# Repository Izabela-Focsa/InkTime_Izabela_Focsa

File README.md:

# InkTime Smartwatch - Dispozitiv Wearable Open Source (Stadiu EVT)

## 📌 Prezentare Generală

**InkTime** este un smartwatch open-source, proiectat în jurul microcontrolerului **Nordic nRF52840**, cu accent pe consum redus de energie, conectivitate Bluetooth Low Energy și modularitate hardware.

Acest repository conține:

* designul PCB (Fusion Electronics)
* fișierele pentru fabricație (Gerber, BOM, Pick & Place)
* designul mecanic (Fusion 360)
* integrarea sistemului pentru etapa EVT (Engineering Validation Test)

---

## 🧩 Diagrama Bloc a Sistemului

Arhitectura sistemului este centrată în jurul microcontrolerului nRF52840, care gestionează comunicația, afișajul și senzorii.

```
        +----------------------+
        |     Baterie LiPo     |
        +----------+-----------+
                   |
            +------v------+
            |  BQ25180    |  (Încărcare)
            +------+------+
                   |
            +------v------+
            |  RT6160A    |  (Regulator 3.3V)
            +------+------+
                   |
         +---------v---------+
         |    nRF52840 MCU   |
         | (BLE + Procesare) |
         +---+----+----+-----+
             |    |    |
        SPI  |    |    | I2C
             |    |    |
   +---------v+  |   +v-----------+
   | Display   |  |   | BMA423 IMU|
   | E-Paper   |  |   +------------+
   +----------+  |
                 |
             +---v---------+
             | MAX17048    |
             | Fuel Gauge  |
             +-------------+

             +-------------+
             | DRV2605L    |
             | Vibrații    |
             +-------------+

             +-------------+
             | Butoane     |
             +-------------+
```

---

## 🔌 Funcționalitatea Hardware (Detaliat)

### 🧠 Microcontroler – nRF52840

* ARM Cortex-M4F @ 64 MHz
* Bluetooth Low Energy 5.0 integrat
* Consum foarte redus în mod sleep

Roluri principale:

* procesare date senzori
* control display
* comunicare BLE

---

### 📺 Display – E-Paper

* Interfață: **SPI**
* Consum foarte mic
* Ideal pentru afișare permanentă

---

### ⚡ Managementul Energiei

#### 🔋 BQ25180

* gestionează încărcarea bateriei LiPo
* alimentare prin USB (VBUS)

#### 🔌 RT6160A

* convertor Buck-Boost
* furnizează **3.3V stabil**
* permite funcționarea chiar și la tensiuni scăzute ale bateriei

---

### 📊 Senzori și Actuatori

#### BMA423 (Accelerometru)

* interfață I2C
* detectare mișcare / pași

#### MAX17048 (Fuel Gauge)

* monitorizare nivel baterie
* consum foarte redus

#### DRV2605L (Driver Haptic)

* controlează motorul de vibrații
* suportă feedback haptic avansat

---

### 🎮 Input Utilizator

* 3 butoane: UP / ENTER / DOWN
* conectate ca GPIO cu rezistențe pull-up interne

---

## 🔗 Mapare Pini nRF52840

| Componentă          | Pini                                                                          | Interfață | Motiv                  |
| ------------------- | ----------------------------------------------------------------------------- | --------- | ---------------------- |
| **Display E-Paper** | P0.28 (SCK), P0.29 (MOSI), P0.30 (CS), P0.31 (D/C), P0.02 (RST), P0.03 (BUSY) | SPI       | Transfer rapid de date |
| **Butoane**         | P0.08, P0.11, P0.12                                                           | GPIO      | Input simplu           |
| **Haptic Driver**   | P0.16                                                                         | GPIO/PWM  | Control vibrații       |
| **Senzori I2C**     | P0.14 (SDA), P0.15 (SCL)                                                      | I2C       | Magistrală comună      |
| **Fuel Gauge**      | I2C                                                                           | I2C       | Monitorizare baterie   |

---

## 📦 Bill of Materials (BOM)

| Ref  | Componentă | Link JLCPCB                                             | Datasheet                                                                                      |
| ---- | ---------- | ------------------------------------------------------- | ---------------------------------------------------------------------------------------------- |
| U1   | nRF52840   | https://jlcpcb.com/partdetail/Nordic-nRF52840           | https://infocenter.nordicsemi.com/pdf/nRF52840_PS_v1.1.pdf                                     |
| U2   | DRV2605L   | https://jlcpcb.com/partdetail/TexasInstruments-DRV2605L | https://www.ti.com/lit/ds/symlink/drv2605l.pdf                                                 |
| U3   | MAX17048   | https://jlcpcb.com/partdetail/MaximIntegrated-MAX17048  | https://datasheets.maximintegrated.com/en/ds/MAX17048-MAX17049.pdf                             |
| IC1  | BQ25180    | https://jlcpcb.com/partdetail/TexasInstruments-BQ25180  | https://www.ti.com/lit/ds/symlink/bq25180.pdf                                                  |
| IC2  | BMA423     | https://jlcpcb.com/partdetail/Bosch-BMA423              | https://www.bosch-sensortec.com/media/boschsensortec/downloads/datasheets/bst-bma423-ds000.pdf |
| IC3  | RT6160A    | https://jlcpcb.com/partdetail/Richtek-RT6160A           | https://www.richtek.com/assets/product_file/RT6160A/DS6160A-00.pdf                             |
| ANT1 | Antenă BLE | https://jlcpcb.com                                      |                                                                          |

---

## ⚙️ Constrângeri și Decizii de Design

### PCB

* trasee alimentare: **0.3 mm**
* trasee semnal: **0.15 mm**
* PCB pe 2 straturi

### RF

* plan de masă continuu
* zonă fără cupru sub antenă

### Decuplare

* condensatori 100nF la <1mm de fiecare IC

### Mecanic

* toate componentele pe **TOP layer**
* design compact pentru carcasă

---

## 🔋 Estimare Consum Energetic

| Mod                   | Consum    |
| --------------------- | --------- |
| Activ (BLE + display) | ~15–20 mA |
| Idle                  | ~2–5 mA   |
| Sleep                 | <10 µA    |

Baterie: ~200–300 mAh
Autonomie estimată: **2–5 zile**

---

## 🖼️ Randări și Design

Randările dispozitivului, ale PCB-ului și integrarea în carcasă pot fi găsite în folderul dedicat din repository:

👉 [Images Folder](./Images)

---

## 🛠️ Fișiere pentru Fabricație

* Gerber
* Drill files
* Pick & Place (.csv)
* BOM (.csv)

---

## 📘 Design Log

* realizare schemă electronică
* rutare PCB completă
* verificare DRC
* integrare mecanică finală

---

## 📄 Licență

Proiectul este licențiat sub **GNU General Public License v3.0**.

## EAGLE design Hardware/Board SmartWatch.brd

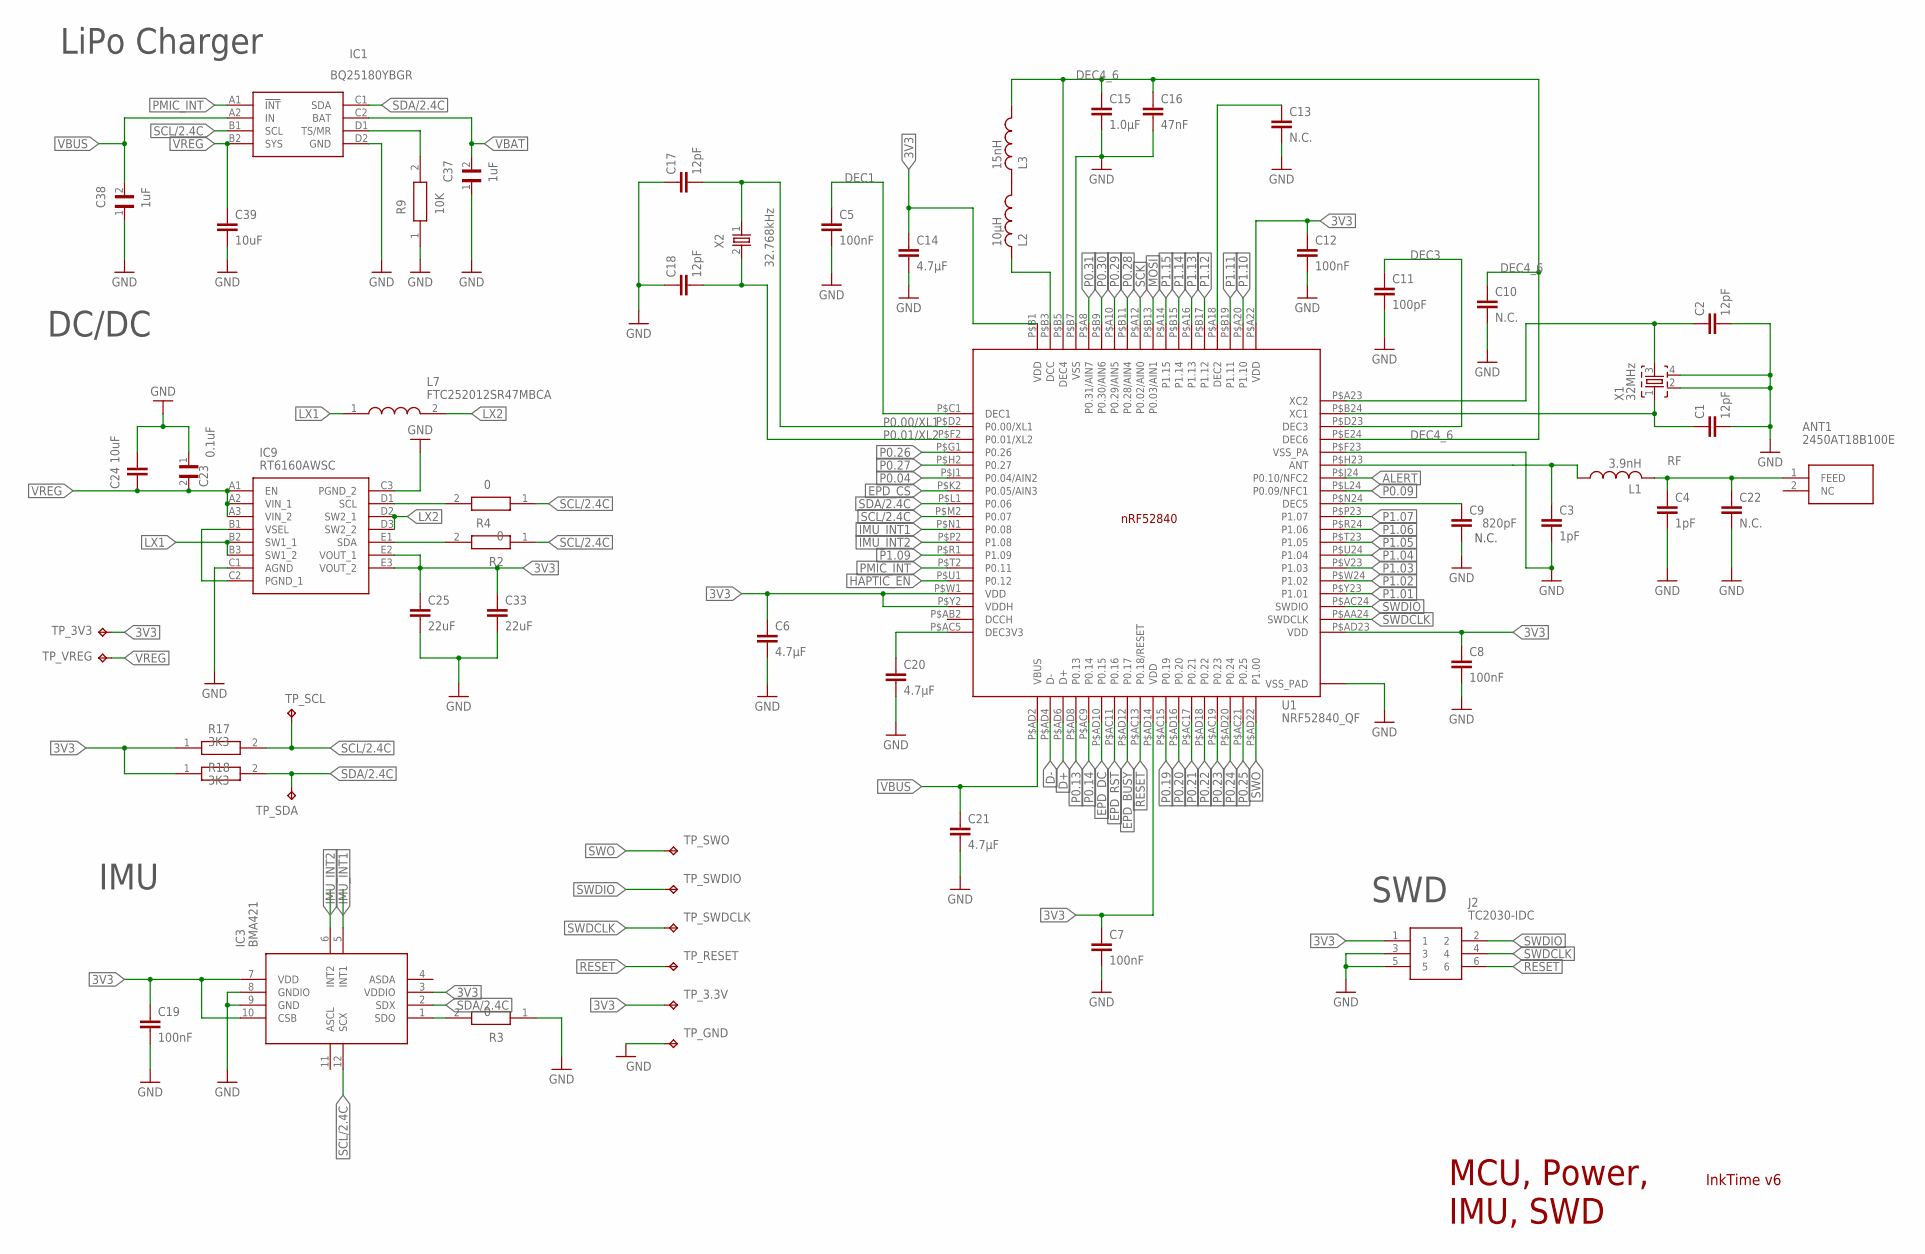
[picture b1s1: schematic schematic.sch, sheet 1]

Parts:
ANT1: 2450AT18B100E; 2450AT18B100E_ANTC3216X140N
C1, C2, C17, C18: 12pF; NORDIC_NRF_3_RESC0201_L
C3, C4: 1pF; NORDIC_NRF_3_RESC0201_L
C5, C7, C8, C12, C19: 100nF; NORDIC_NRF_3_RESC0201_L
C6, C14, C20, C21: 4.7µF; NORDIC_NRF_3_RESC0402_L
C9: 820pF; NORDIC_NRF_3_RESC0201_L
C10, C13, C22: N.C.; NORDIC_NRF_3_RESC0201_L
C11: 100pF; NORDIC_NRF_3_RESC0201_L
C15: 1.0µF; NORDIC_NRF_3_RESC0402_L
C16: 47nF; NORDIC_NRF_3_RESC0201_L
C23: 0.1uF; GRM011R60J152KE01L_2_CAPC0201X13N
C24: 10uF; NORDIC_NRF_3_RESC0201_L
C25, C33: 22uF; NORDIC_NRF_3_RESC0201_L
C37, C38: 1uF; GRM011R60J152KE01L_2_CAPC0201X13N
C39: 10uF; PERFECT_0402_0402
IC1: BQ25180YBGR_BQ25180YBGR; BQ25180YBGR_BGA8C40P2X4_100X155X50
IC3: BMA421; BMA423_BMA423
IC9: RT6160AWSC; RT6160AWSC_BGA15C40P3X5_140X230X60
J2: TC2030-IDC; TC2030-IDC_TC2030IDC
L1: 3.9nH; NORDIC_NRF_2_RESC0402_L
L2: 10µH; NORDIC_NRF_2_RESC0402_L
L3: 15nH; NORDIC_NRF_2_RESC0402_L
L7: FTC252012SR47MBCA; MLP2016SR47MT0S1_INDC2016X100N
R2, R4: 0; CPF0201D7K68C1_0201
R3: 0; ERA-1AEB3401C_0201
R9: 10K; ERA-1AEB3401C_0201
R17, R18: 3K3; CPF0201D7K68C1_0201
TP_3.3V, TP_3V3: HECTOR_WATCH_1_TPTP20R; HECTOR_WATCH_1_TP20R
TP_GND: HECTOR_WATCH_1_TPTP20R; HECTOR_WATCH_1_TP20R
TP_RESET: HECTOR_WATCH_1_TPTP20R; HECTOR_WATCH_1_TP20R
TP_SCL: HECTOR_WATCH_1_TPTP20R; HECTOR_WATCH_1_TP20R
TP_SDA: HECTOR_WATCH_1_TPTP20R; HECTOR_WATCH_1_TP20R
TP_SWDCLK: HECTOR_WATCH_1_TPTP20R; HECTOR_WATCH_1_TP20R
TP_SWDIO: HECTOR_WATCH_1_TPTP20R; HECTOR_WATCH_1_TP20R
TP_SWO: HECTOR_WATCH_1_TPTP20R; HECTOR_WATCH_1_TP20R
TP_VREG: HECTOR_WATCH_1_TPTP20R; HECTOR_WATCH_1_TP20R
U1: NRF52840_QF; NORDIC_NRF_4_AQFN50P700X700X85_HS-74N
X1: 32MHz; NORDIC_NRF_BT-XTAL_2016_N
X2: 32.768kHz; NORDIC_NRF_1_XTAL_3215_N

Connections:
3V3: C6.1, C7.1, C8.1, C12.1, C14.1, C19.1, C25.1, C33.1, IC3.3 (VDDIO), IC3.7 (VDD), IC3.10 (CSB), IC9.E2 (VOUT_1), IC9.E3 (VOUT_2), J2.1, R17.1, R18.1, TP_3.3V.TP, TP_3V3.TP, U1.P$A22 (VDD), U1.P$AD14 (VDD), U1.P$AD23 (VDD), U1.P$B1 (VDD), U1.P$W1 (VDD), U1.P$Y2 (VDDH); also elsewhere on the board
ALERT: U1.P$J24 (P0.10/NFC2); also elsewhere on the board
D+: U1.P$AD6 (D+); also elsewhere on the board
D-: U1.P$AD4 (D-); also elsewhere on the board
DEC1: C5.1, U1.P$C1 (DEC1)
DEC3: C11.1, U1.P$D23 (DEC3)
DEC4_6: C10.1, C15.1, C16.1, L3.1, U1.P$B5 (DEC4), U1.P$E24 (DEC6)
EPD_BUSY: U1.P$AD12 (P0.17); also elsewhere on the board
EPD_CS: U1.P$K2 (P0.05/AIN3); also elsewhere on the board
EPD_DC: U1.P$AD10 (P0.15); also elsewhere on the board
EPD_RST: U1.P$AC11 (P0.16); also elsewhere on the board
GND: C1.2, C2.2, C3.2, C4.2, C5.2, C6.2, C7.2, C8.2, C9.2, C10.2, C11.2, C12.2, C13.2, C14.2, C15.2, C16.2, C17.1, C18.1, C19.2, C20.2, C21.2, C22.2, C23.1, C24.1, C25.2, C33.2, C37.1, C38.1, C39.2, IC1.D2 (GND), IC3.8 (GNDIO), IC3.9 (GND), IC9.C1 (AGND), IC9.C3 (PGND_2), J2.3, J2.5, R3.1, R9.1, TP_GND.TP, U1.P$74 (VSS_PAD), U1.P$75 (VSS_PAD), U1.P$76 (VSS_PAD), U1.P$77 (VSS_PAD), U1.P$78 (VSS_PAD), U1.P$79 (VSS_PAD), U1.P$80 (VSS_PAD), U1.P$81 (VSS_PAD), U1.P$82 (VSS_PAD), U1.P$83 (VSS_PAD), U1.P$84 (VSS_PAD), U1.P$85 (VSS_PAD), U1.P$86 (VSS_PAD), U1.P$87 (VSS_PAD), U1.P$88 (VSS_PAD), U1.P$89 (VSS_PAD), U1.P$90 (VSS_PAD), U1.P$B7 (VSS), U1.P$F23 (VSS_PA), X1.2, X1.4; also elsewhere on the board
HAPTIC_EN: U1.P$U1 (P0.12); also elsewhere on the board
IMU_INT1: IC3.5 (INT1), U1.P$N1 (P0.08)
IMU_INT2: IC3.6 (INT2), U1.P$P2 (P1.08)
LX1: IC9.B2 (SW1_1), IC9.B3 (SW1_2), L7.1
LX2: IC9.D2 (SW2_1), IC9.D3 (SW2_2), L7.2
MOSI: U1.P$B13 (P0.03/AIN1); also elsewhere on the board
unnamed: IC9.B1 (VSEL), IC9.C2 (PGND_1)
unnamed: C3.1, L1.1, U1.P$H23 (ANT)
unnamed: C1.1, U1.P$B24 (XC1), X1.1
unnamed: C2.1, U1.P$A23 (XC2), X1.3
unnamed: IC9.D1 (SCL), R4.2
unnamed: IC1.D1 (TS/MR), R9.2
unnamed: IC3.1 (SDO), R3.2
unnamed: IC9.E1 (SDA), R2.2
unnamed: L2.2, U1.P$B3 (DCC)
unnamed: L2.1, L3.2
unnamed: C20.1, U1.P$AC5 (DEC3V3)
unnamed: C9.1, U1.P$N24 (DEC5)
unnamed: C13.1, U1.P$A18 (DEC2)
P0.00/XL1: C17.2, U1.P$D2 (P0.00/XL1), X2.1
P0.01/XL2: C18.2, U1.P$F2 (P0.01/XL2), X2.2
P0.04: U1.P$J1 (P0.04/AIN2)
P0.09: U1.P$L24 (P0.09/NFC1)
P0.13: U1.P$AD8 (P0.13)
P0.14: U1.P$AC9 (P0.14)
P0.19: U1.P$AC15 (P0.19)
P0.20: U1.P$AD16 (P0.20)
P0.21: U1.P$AC17 (P0.21)
P0.22: U1.P$AD18 (P0.22)
P0.23: U1.P$AC19 (P0.23)
P0.24: U1.P$AD20 (P0.24)
P0.25: U1.P$AC21 (P0.25)
P0.26: U1.P$G1 (P0.26)
P0.27: U1.P$H2 (P0.27)
P0.28: U1.P$B11 (P0.28/AIN4)
P0.29: U1.P$A10 (P0.29/AIN5)
P0.30: U1.P$B9 (P0.30/AIN6)
P0.31: U1.P$A8 (P0.31/AIN7)
P1.01: U1.P$Y23 (P1.01)
P1.02: U1.P$W24 (P1.02)
P1.03: U1.P$V23 (P1.03)
P1.04: U1.P$U24 (P1.04)
P1.05: U1.P$T23 (P1.05)
P1.06: U1.P$R24 (P1.06)
P1.07: U1.P$P23 (P1.07)
P1.09: U1.P$R1 (P1.09)
P1.10: U1.P$A20 (P1.10)
P1.11: U1.P$B19 (P1.11)
P1.12: U1.P$B17 (P1.12)
P1.13: U1.P$A16 (P1.13)
P1.14: U1.P$B15 (P1.14)
P1.15: U1.P$A14 (P1.15)
PMIC_INT: IC1.A1 (!INT), U1.P$T2 (P0.11)
RESET: J2.6, TP_RESET.TP, U1.P$AC13 (P0.18/RESET)
RF: ANT1.1 (FEED), C4.1, C22.1, L1.2
SCK: U1.P$A12 (P0.02/AIN0); also elsewhere on the board
SCL/2.4C: IC1.B1 (SCL), IC3.12 (SCX), R2.1, R4.1, R17.2, TP_SCL.TP, U1.P$M2 (P0.07)
SDA/2.4C: IC1.C1 (SDA), IC3.2 (SDX), R18.2, TP_SDA.TP, U1.P$L1 (P0.06)
SWDCLK: J2.4, TP_SWDCLK.TP, U1.P$AA24 (SWDCLK)
SWDIO: J2.2, TP_SWDIO.TP, U1.P$AC24 (SWDIO)
SWO: TP_SWO.TP, U1.P$AD22 (P1.00)
VBAT: C37.2, IC1.C2 (BAT); also elsewhere on the board
VBUS: C21.1, C38.2, IC1.A2 (IN), U1.P$AD2 (VBUS); also elsewhere on the board
VREG: C23.2, C24.2, C39.1, IC1.B2 (SYS), IC9.A1 (EN), IC9.A2 (VIN_1), IC9.A3 (VIN_2), TP_VREG.TP

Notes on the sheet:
N.C.
LiPo Charger
DC/DC
IMU
SWD
MCU, Power, IMU, SWD
InkTime v6

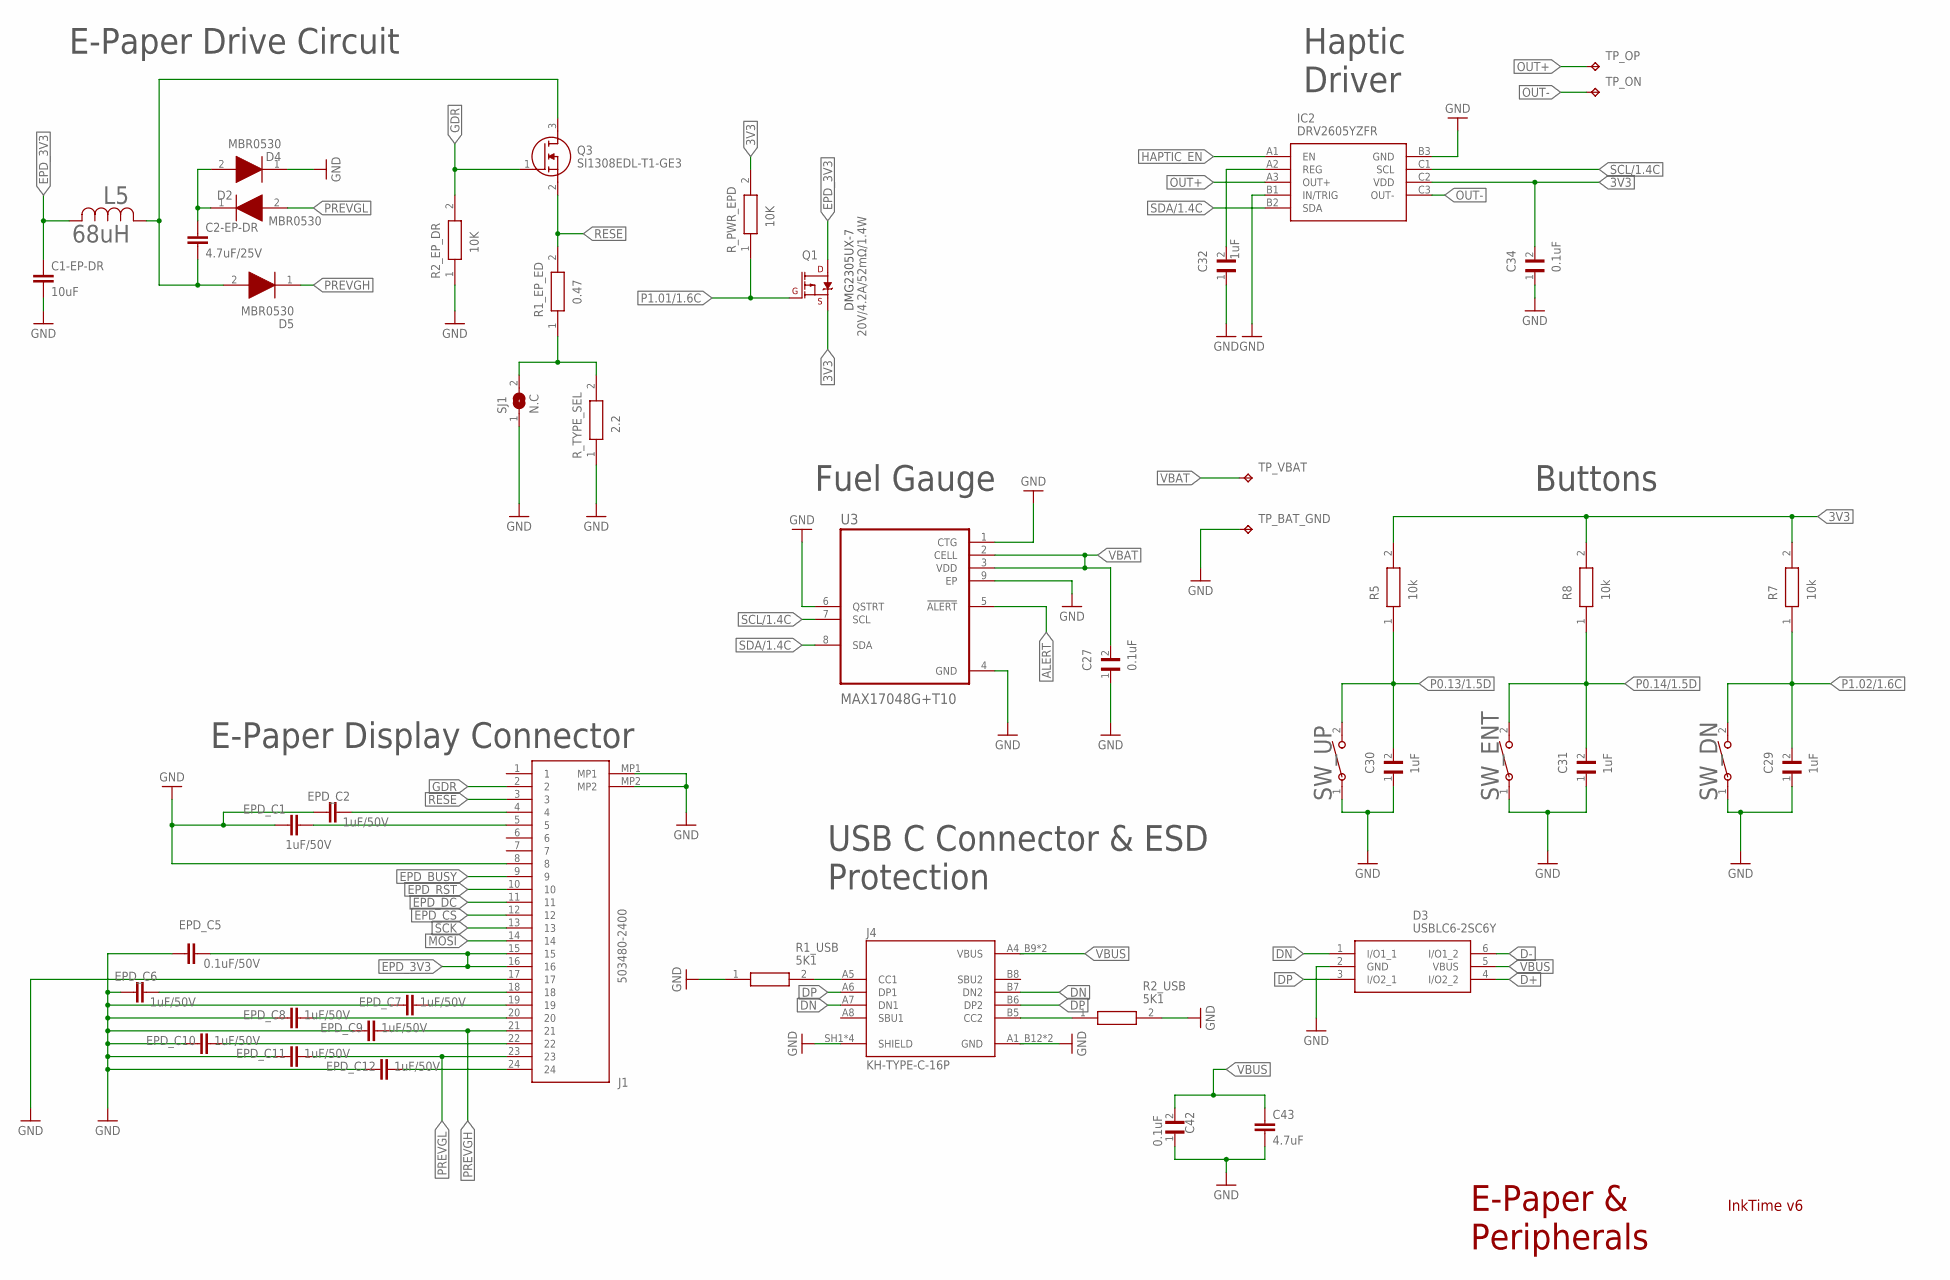
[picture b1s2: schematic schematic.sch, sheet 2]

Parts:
C1-EP-DR: 10uF; NORDIC_NRF_3_RESC0402_L
C2-EP-DR: 4.7uF/25V; NORDIC_NRF_3_RESC0402_L
C27, C34, C42: 0.1uF; GRM011R60J152KE01L_2_CAPC0201X13N
C29, C30, C31, C32: 1uF; GRM011R60J152KE01L_2_CAPC0201X13N
C43: 4.7uF; NORDIC_NRF_3_RESC0402_L
D2, D4, D5: MBR0530; ESP32_C6_LIBRARY_5_SOD3716X135N
D3: USBLC6-2SC6Y; ESP32_C6_LIBRARY_3_SOT95P280X145-6N
EPD_C1, EPD_C2: 1uF/50V; NORDIC_NRF_3_RESC0201_L
EPD_C5: 0.1uF/50V; NORDIC_NRF_3_RESC0201_L
EPD_C6, EPD_C7, EPD_C8, EPD_C9, EPD_C10, EPD_C11, EPD_C12: 1uF/50V; NORDIC_NRF_3_RESC0402_L
IC2: DRV2605YZFR; DRV2605YZFR_BGA9C50P3X3_144X144X62
J1: 503480-2400; 503480-2400_5034802400
J4: KH-TYPE-C-16P; KH-TYPE-C-16P_KINGHELM_KH-TYPE-C-16P
L5: 68uH; ESP32_C6_LIBRARY_2_IND_4828-WE-TPC_WRE
Q1: 20V/4.2A/52mΩ/1.4W; ESP32_C6_LIBRARY_4_ESP32_C6_LIBRARY_4_ESP32_C6_LIBRARY_4_ES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
Q3: SI1308EDL-T1-GE3; ESP32_C6_LIBRARY_6_SOT65P210X110-3N
R1_EP_ED: 0.47; CPF0201D7K68C1_0201
R1_USB, R2_USB: 5K1; CPF0201D7K68C1_0201
R2_EP_DR: 10K; CPF0201D7K68C1_0201
R5, R7, R8: 10k; ERA-1AEB3401C_0201
R_PWR_EPD: 10K; CPF0201D7K68C1_0201
R_TYPE_SEL: 2.2; CPF0201D7K68C1_0201
SJ1: N.C; ESP32_C6_LIBRARY_7_JUMPER_SJ
SW_DN: 2025-10-22_07-23-44_LIBRARY_EVP-AKE31ASW_EVP-AKE3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; 2025-10-22_07-23-44_LIBRARY_SW_EVP-AKE31A_PAN
SW_ENT: 2025-10-22_07-23-44_LIBRARY_EVP-AKE31ASW_EVP-AKE3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; 2025-10-22_07-23-44_LIBRARY_SW_EVP-AKE31A_PAN
SW_UP: 2025-10-22_07-23-44_LIBRARY_EVP-AKE31ASW_EVP-AKE3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; 2025-10-22_07-23-44_LIBRARY_SW_EVP-AKE31A_PAN
TP_BAT_GND: HECTOR_WATCH_1_TPTP20R; HECTOR_WATCH_1_TP20R
TP_ON: HECTOR_WATCH_1_TPTP20R; HECTOR_WATCH_1_TP20R
TP_OP: HECTOR_WATCH_1_TPTP20R; HECTOR_WATCH_1_TP20R
TP_VBAT: HECTOR_WATCH_1_TPTP20R; HECTOR_WATCH_1_TP20R
U3: MAX17048G+T10; ESP32_C6_LIBRARY_SON50P200X200X80-9N

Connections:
3V3: C34.2, IC2.C2 (VDD), Q1.2 (S), R5.2, R7.2, R8.2, R_PWR_EPD.2; also elsewhere on the board
ALERT: U3.5 (!ALERT); also elsewhere on the board
D+: D3.4 (I/O2_2); also elsewhere on the board
D-: D3.6 (I/O1_2); also elsewhere on the board
DN: D3.1 (I/O1_1), J4.A7 (DN1), J4.B7 (DN2)
DP: D3.3 (I/O2_1), J4.A6 (DP1), J4.B6 (DP2)
EPD_3V3: C1-EP-DR.1, EPD_C5.2, J1.15, J1.16, L5.2, Q1.3 (D)
EPD_BUSY: J1.9; also elsewhere on the board
EPD_CS: J1.12; also elsewhere on the board
EPD_DC: J1.11; also elsewhere on the board
EPD_RST: J1.10; also elsewhere on the board
GDR: J1.2, Q3.1 (G), R2_EP_DR.2
GND: C1-EP-DR.2, C27.1, C29.1, C30.1, C31.1, C32.1, C34.1, C42.1, C43.2, D3.2 (GND), D4.1 (K), EPD_C1.1, EPD_C2.1, EPD_C5.1, EPD_C6.1, EPD_C7.1, EPD_C8.1, EPD_C9.1, EPD_C10.1, EPD_C11.1, EPD_C12.1, IC2.B1 (IN/TRIG), IC2.B3 (GND), J1.8, J1.17, J1.MP1, J1.MP2, J4.A1_B12 (GND), J4.A12_B1 (GND), J4.SH1 (SHIELD), J4.SH2 (SHIELD), J4.SH3 (SHIELD), J4.SH4 (SHIELD), R1_USB.1, R2_EP_DR.1, R2_USB.2, R_TYPE_SEL.1, SJ1.1, SW_DN.1, SW_ENT.1, SW_UP.1, TP_BAT_GND.TP, U3.1 (CTG), U3.4 (GND), U3.6 (QSTRT), U3.9 (EP); also elsewhere on the board
HAPTIC_EN: IC2.A1 (EN); also elsewhere on the board
MOSI: J1.14; also elsewhere on the board
unnamed: C2-EP-DR.2, D5.2 (A), L5.1, Q3.3 (D)
unnamed: C2-EP-DR.1, D2.1 (K), D4.2 (A)
unnamed: R1_EP_ED.1, R_TYPE_SEL.2, SJ1.2
unnamed: EPD_C2.2, J1.4
unnamed: C32.2, IC2.A2 (REG)
unnamed: EPD_C1.2, J1.5
unnamed: EPD_C6.2, J1.18
unnamed: EPD_C7.2, J1.19
unnamed: EPD_C8.2, J1.20
unnamed: EPD_C10.2, J1.22
unnamed: J4.A5 (CC1), R1_USB.2
unnamed: EPD_C12.2, J1.24
unnamed: J4.B5 (CC2), R2_USB.1
OUT+: IC2.A3 (OUT+), TP_OP.TP
OUT-: IC2.C3 (OUT-), TP_ON.TP
P0.13/1.5D: C30.2, R5.1, SW_UP.2
P0.14/1.5D: C31.2, R8.1, SW_ENT.2
P1.01/1.6C: Q1.1 (G), R_PWR_EPD.1
P1.02/1.6C: C29.2, R7.1, SW_DN.2
PREVGH: D5.1 (K), EPD_C9.2, J1.21
PREVGL: D2.2 (A), EPD_C11.2, J1.23
RESE: J1.3, Q3.2 (S), R1_EP_ED.2
SCK: J1.13; also elsewhere on the board
SCL/1.4C: IC2.C1 (SCL), U3.7 (SCL)
SDA/1.4C: IC2.B2 (SDA), U3.8 (SDA)
VBAT: C27.2, TP_VBAT.TP, U3.2 (CELL), U3.3 (VDD); also elsewhere on the board
VBUS: C42.2, C43.1, D3.5 (VBUS), J4.A4_B9 (VBUS), J4.A9_B4 (VBUS); also elsewhere on the board

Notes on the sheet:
DMG2305UX-7
E-Paper Drive Circuit
Haptic Driver
Fuel Gauge
Buttons
E-Paper Display Connector
USB C Connector & ESD Protection
E-Paper & Peripherals
InkTime v6

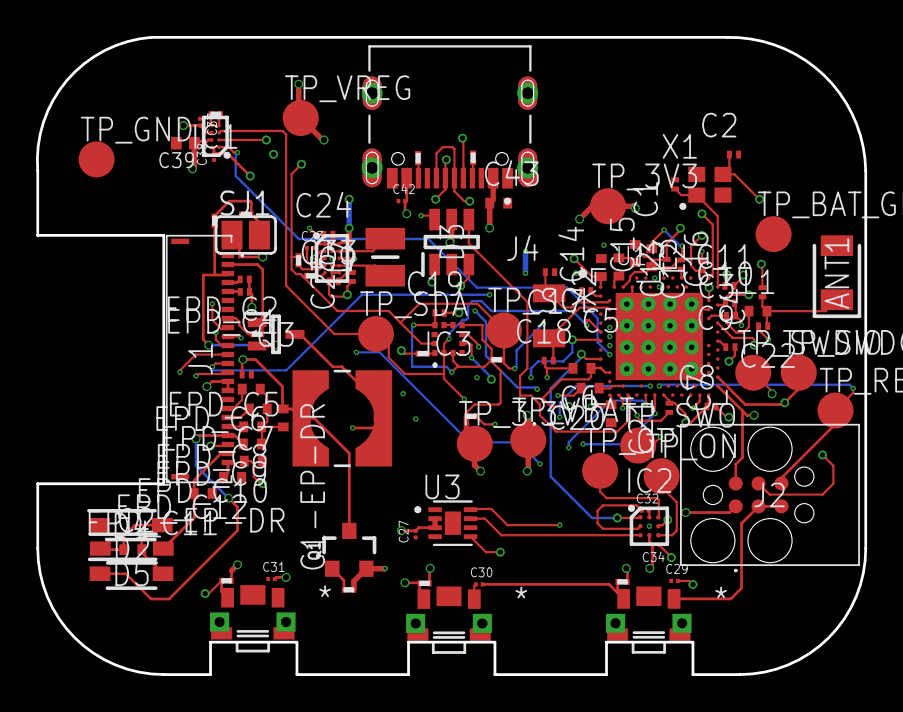
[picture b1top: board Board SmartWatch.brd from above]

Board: 2 copper layers, 46.0 x 35.4 mm, 105 parts (0 on the bottom side), 73 nets.

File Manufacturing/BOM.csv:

Reference Designators;Quantity;Description;Package;Value;Manufacturer;Manufacturer Part Number;Vendor;Vendor Part Number;Top/Bottom;
;1;Board;Board;;;;;;;
ANT1;1;Antennas 2.45GHz ANTENNA;2450AT18B100E_ANTC3216X140N;2450AT18B100E;;;;;Top;
C1, C2, C17, C18;4;Generic chip capacitor;NORDIC_NRF_3_RESC0201_L;12pF;;;;;Top;
C1-EP-DR;1;Generic chip capacitor;NORDIC_NRF_3_RESC0402_L;10uF;;;;;Top;
C2-EP-DR;1;Generic chip capacitor;NORDIC_NRF_3_RESC0402_L;4.7uF/25V;;;;;Top;
C3, C4;2;Generic chip capacitor;NORDIC_NRF_3_RESC0201_L;1pF;;;;;Top;
C5, C7, C8, C12, C19;5;Generic chip capacitor;NORDIC_NRF_3_RESC0201_L;100nF;;;;;Top;
C6, C14, C20, C21;4;Generic chip capacitor;NORDIC_NRF_3_RESC0402_L;4.7µF;;;;;Top;
C9;1;Generic chip capacitor;NORDIC_NRF_3_RESC0201_L;820pF;;;;;Top;
C10, C13, C22;3;Generic chip capacitor;NORDIC_NRF_3_RESC0201_L;N.C.;;;;;Top;
C11;1;Generic chip capacitor;NORDIC_NRF_3_RESC0201_L;100pF;;;;;Top;
C15;1;Generic chip capacitor;NORDIC_NRF_3_RESC0402_L;1.0µF;;;;;Top;
C16;1;Generic chip capacitor;NORDIC_NRF_3_RESC0201_L;47nF;;;;;Top;
C23, C27, C34, C42;4;Check availability;CAPC0201X13N;0.1uF;;;;;Top;
C24;1;Generic chip capacitor;NORDIC_NRF_3_RESC0201_L;10uF;;;;;Top;
C25, C33;2;Generic chip capacitor;NORDIC_NRF_3_RESC0201_L;22uF;;;;;Top;
C29, C30, C31, C32, C37, C38;6;Check availability;CAPC0201X13N;1uF;;;;;Top;
C39;1;0402 (1005 Metric);PERFECT_0402_0402;10uF;;;;;Top;
C43;1;Generic chip capacitor;NORDIC_NRF_3_RESC0402_L;4.7uF;;;;;Top;
D2, D4, D5;3;ON SEMICONDUCTOR - MBR0530 - DIODE, SCHOTTKY, 0.5A, 30V, SOD-123;SOD3716X135N;MBR0530;;;;;Top;
D3;1;Low Cap. ESD Protection Auto SOT-23-6 STMicroelectronics USBLC6-2SC6Y, Dual Uni-Directional TVS Diode Array, 6-Pin SOT-23;SOT95P280X145-6N;USBLC6-2SC6Y;;;;;Top;
EPD_C1, EPD_C2;2;Generic chip capacitor;NORDIC_NRF_3_RESC0201_L;1uF/50V;;;;;Top;
EPD_C5;1;Generic chip capacitor;NORDIC_NRF_3_RESC0201_L;0.1uF/50V;;;;;Top;
EPD_C6, EPD_C7, EPD_C8, EPD_C9, EPD_C10, EPD_C11, EPD_C12;7;Generic chip capacitor;NORDIC_NRF_3_RESC0402_L;1uF/50V;;;;;Top;
IC1;1;Charger IC Lithium Ion/Polymer, Lithium Iron Phosphate 8-DSBGA (1.6x1.1);BQ25180YBGR_BGA8C40P2X4_100X155X50;BQ25180YBGR_BQ25180YBGR;;;;;Top;
IC2;1;Haptic Driver for ERM/LRA with Built-In Library and Smart Loop Architecture;DRV2605YZFR_BGA9C50P3X3_144X144X62;DRV2605YZFR;;;;;Top;
IC3;1;Accelerometers Triaxial low-g 12bit Acceleration Sensor;BMA423_BMA423;BMA421;;;;;Top;
IC9;1;Buck-Boost Regulator Positive Output Step-Up/Step-Down I2C DC-DC Controller IC 15-WL-CSP (BSC) (1.4x2.3);RT6160AWSC_BGA15C40P3X5_140X230X60;RT6160AWSC;;;;;Top;
J1;1;FFC & FPC Connectors 0.5mm FPC RA SMT Dual Contact 24Ckt;503480-2400_5034802400;503480-2400;;;;;Top;
J2;1;CABLE ADAPTER 6 POS;TC2030-IDC_TC2030IDC;TC2030-IDC;;;;;Top;
J4;1;Check availability;KINGHELM_KH-TYPE-C-16P;KH-TYPE-C-16P;;;;;Top;
L1;1;Generic chip inductor;NORDIC_NRF_2_RESC0402_L;3.9nH;;;;;Top;
L2;1;Generic chip inductor;NORDIC_NRF_2_RESC0402_L;10µH;;;;;Top;
L3;1;Generic chip inductor;NORDIC_NRF_2_RESC0402_L;15nH;;;;;Top;
L5;1;;ESP32_C6_LIBRARY_2_IND_4828-WE-TPC_WRE;68uH;;;;;Top;
L7;1;SMD / SMT Inductors (Coils), L=0.47?H, L x W x T :;MLP2016SR47MT0S1_INDC2016X100N;FTC252012SR47MBCA;;;;;Top;
Q1;1;P-channel MOSFETs;ESP32_WROVER_SPARKFUN-DISCRETESEMI_SOT23-3;20V/4.2A/52mΩ/1.4W;;;;;Top;
Q3;1;MOSFET N-Ch 30V 1.5A TrenchFET SC70 Vishay Si1308EDL-T1-GE3 N-channel MOSFET Transistor, 1.5 A, 30 V, 3-Pin SC-70;SOT65P210X110-3N;SI1308EDL-T1-GE3;;;;;Top;
R_PWR_EPD, R2_EP_DR;2;7.68k 0201 Thin Film Surface Mount Fixed Resistor +/-0.5% 0.031W CPF0201D7K68C1;CPF0201D7K68C1_0201;10K;;;;;Top;
R_TYPE_SEL;1;7.68k 0201 Thin Film Surface Mount Fixed Resistor +/-0.5% 0.031W CPF0201D7K68C1;CPF0201D7K68C1_0201;2.2;;;;;Top;
R1_EP_ED;1;7.68k 0201 Thin Film Surface Mount Fixed Resistor +/-0.5% 0.031W CPF0201D7K68C1;CPF0201D7K68C1_0201;0.47;;;;;Top;
R1_USB, R2_USB;2;7.68k 0201 Thin Film Surface Mount Fixed Resistor +/-0.5% 0.031W CPF0201D7K68C1;CPF0201D7K68C1_0201;5K1;;;;;Top;
R2, R4;2;7.68k 0201 Thin Film Surface Mount Fixed Resistor +/-0.5% 0.031W CPF0201D7K68C1;CPF0201D7K68C1_0201;0;;;;;Top;
R3;1;7.68k 0201 Thin Film Surface Mount Fixed Resistor +/-0.5% 0.031W CPF0201D7K68C1;R0201;0;;;;;Top;
R5, R7, R8;3;7.68k 0201 Thin Film Surface Mount Fixed Resistor +/-0.5% 0.031W CPF0201D7K68C1;R0201;10k;;;;;Top;
R9;1;7.68k 0201 Thin Film Surface Mount Fixed Resistor +/-0.5% 0.031W CPF0201D7K68C1;R0201;10K;;;;;Top;
R17, R18;2;7.68k 0201 Thin Film Surface Mount Fixed Resistor +/-0.5% 0.031W CPF0201D7K68C1;CPF0201D7K68C1_0201;3K3;;;;;Top;
SJ1;1;SMD solder JUMPER;JUMPER_SJ;N.C;;;;;Top;
SW_DN, SW_ENT, SW_UP;3;;SW_EVP-AKE31A_PAN;2025-10-22_07-23-44_LIBRARY_EVP-AKE31ASW_EVP-AKE31A_PAN;;;;;Top;
TP_3.3V, TP_3V3, TP_BAT_GND, TP_GND, TP_ON, TP_OP, TP_RESET, TP_SCL, TP_SDA, TP_SWDCLK, TP_SWDIO, TP_SWO, TP_VBAT, TP_VREG;14;Test pad;HECTOR_WATCH_1_TP20R;HECTOR_WATCH_1_TPTP20R;;;;;Top;
U1;1;nRF52840;NORDIC_NRF_4_AQFN50P700X700X85_HS-74N;NRF52840_QF;;;;;Top;
U3;1;Check availability;SON50P200X200X80-9N;MAX17048G+T10;;;;;Top;
X1;1;;NORDIC_NRF_BT-XTAL_2016_N;32MHz;;;;;Top;
X2;1;;NORDIC_NRF_1_XTAL_3215_N;32.768kHz;;;;;Top;

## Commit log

2026-04-10 Initial commit: Adăugat schematic
2026-04-10 Licenta
2026-04-10 Initialize README with project details and specifications
    Added detailed project overview, hardware architecture, BOM, technical details, and design log for InkTime smartwatch.
2026-04-10 Fix license file reference
    Corrected license file name.
2026-04-20 Toate folderele si fisierele cerute
2026-04-20 Revise README.md
    Updated README.md to provide a detailed overview and specifications for the InkTime smartwatch project
2026-04-20 small change

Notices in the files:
parts and their libraries:
COPYRIGHT: Copyright (C) 2024 Ultra Librarian. All rights reserved.
COPYRIGHT: Copyright (C) 2025 Ultra Librarian. All rights reserved.
